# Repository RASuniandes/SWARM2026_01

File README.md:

# SWARM - Sistema de Control para Robot Móvil

## Descripción General

Este repositorio contiene el sistema completo de control para un robot móvil de 4 ruedas omnidireccionales, desarrollado en la Universidad de los Andes. El proyecto integra:

- **Hardware**: ESP32 con 4 motores DC con encoders y drivers L8871
- **Software**: ROS 2 (Robot Operating System) con múltiples modos de control
- **Sensores**: LiDAR YDLidar para navegación autónoma
- **Visión**: MediaPipe para seguimiento de personas

## Estructura del Proyecto

```
SWARM/
├── ros4meetup/              # Paquete principal ROS2
│   ├── ros4meetup/          # Workspace de ROS2
│   │   ├── src/             # Código fuente
│   │   │   ├── ros4meetup/  # Nodos de control
│   │   │   ├── lidar/       # Driver del LiDAR
│   │   │   └── ...          # Otros paquetes
│   │   └── ...              # Build, install, log
│   └── README.md            # Documentación detallada de ROS2
├── CódigoControl/           # Firmware para ESP32 (Arduino)
├── Control SWARM/           # Diseños de PCB (KiCad)
├── Electrónica/             # Esquemáticos y documentación electrónica
├── Dashboard preliminar/    # Interfaz web de monitoreo
└── ojos_frontales/          # Codigo ESP32 para ojos (Matriz 64x2)
```

## Características Principales

### Modos de Control

1. **Vision** (por defecto): Seguimiento de personas usando MediaPipe
2. **Autonomous**: Navegación autónoma con evitación de obstáculos (LiDAR)
3. **Teleop**: Control manual por teclado (W/A/S/D)
4. **Remote**: Control remoto desde ESP32
5. **Web**: Control desde interfaz web

### Arquitectura

```
[Controladores]  →  [Router]  →  [Serial Bridge]  →  [ESP32]  →  [Motores]
                      ↓ cmd_vel
                  [Comandos de velocidad]
```

Cada controlador publica en su propio topic (`vision_command`, `autonomous_command`, etc.). El **Router** selecciona qué controlador está activo y reenvía sus comandos a `cmd_vel`. El **Serial Bridge** convierte estos comandos a JSON y los envía al ESP32 por puerto serial.

## Inicio Rápido

### Requisitos

- Ubuntu 22.04 o superior
- ROS 2 Humble
- Python 3.10+
- Arduino IDE (para firmware ESP32)

### Instalación

1. **Clonar el repositorio:**
```bash
git clone https://github.com/RASuniandes/SWARM.git
cd SWARM/ros4meetup
```

2. **Configurar el entorno ROS2:**
```bash
source ros4meetup/ros.bash
```

3. **Compilar el workspace:**
```bash
cd ros4meetup
colcon build
source install/setup.bash
```

4. **Cargar firmware en ESP32:**
   - Ver documentación en `ros4meetup/firmware/README.md`

### Ejecución

1. **Iniciar el sistema básico:**
```bash
# Terminal 1: Router
ros2 run ros4meetup router

# Terminal 2: Serial Bridge
ros2 run ros4meetup serial_bridge

# Terminal 3: Controlador (elige uno)
ros2 run ros4meetup vision_controller
# o
ros2 run ros4meetup autonomous_controller
# o
ros2 run ros4meetup teleop_controller
```

2. **Cambiar de modo:**
```bash
ros2 topic pub /config std_msgs/String "data: 'autonomous'" --once
```

## Documentación Adicional

- **ROS2 y Nodos**: Ver `ros4meetup/README.md`
- **Firmware ESP32**: Ver `ros4meetup/firmware/README.md`
- **Electrónica**: Ver `Electrónica/`
- **PCB**: Ver `Control SWARM/`

## Desarrollo

### Estructura de Topics ROS2

- `/cmd_vel` (Twist): Comandos de velocidad final al robot
- `/config` (String): Cambio de modo de control
- `/vision_command` (Twist): Comandos del controlador de visión
- `/autonomous_command` (Twist): Comandos del controlador autónomo
- `/teleop_command` (Twist): Comandos del control por teclado
- `/remote_command` (Twist): Comandos remotos desde ESP32
- `/laser_scan` (LaserScan): Datos del LiDAR
- `/esp_feedback` (String): Retroalimentación del ESP32
- `/faces_direction` (String): Dirección para LEDs faciales

### Hardware

- **Microcontrolador**: ESP32
- **Motores**: 4x DC con reductora 1:80 y encoders (12 PPR)
- **Drivers**: L8871 (H-bridge)
- **Sensor**: YDLidar X4
- **Cámara**: USB o CSI para visión

## Licencia

MIT

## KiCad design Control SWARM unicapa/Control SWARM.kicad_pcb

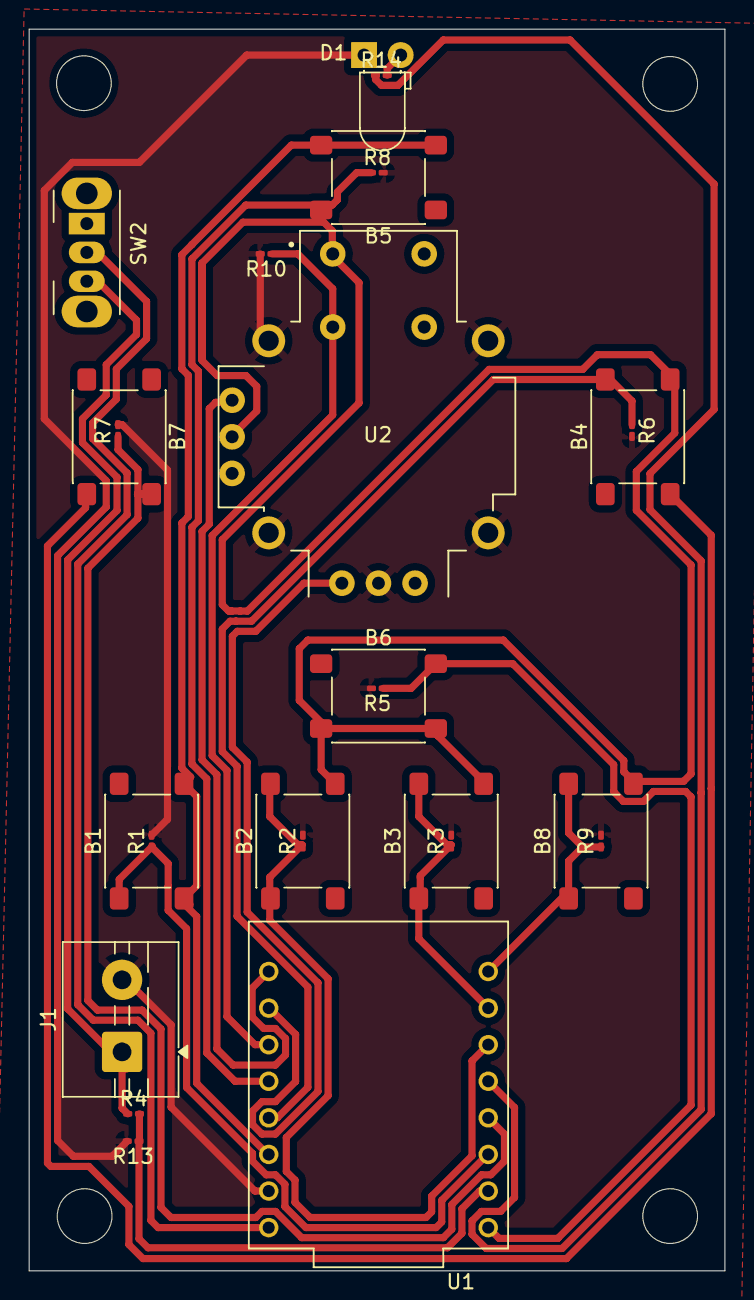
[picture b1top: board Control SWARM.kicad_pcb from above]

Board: 2 copper layers, 48.3 x 86.2 mm, 25 parts (0 on the bottom side), 18 nets.

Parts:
B1: Line Button 1; SW_SPST_PTS645Sx43SMTR92
B2: Line Button 2; SW_SPST_PTS645Sx43SMTR92
B3: Line Button 3; SW_SPST_PTS645Sx43SMTR92
B4: Radial Button 2; SW_SPST_PTS645Sx43SMTR92
B5: Radial Button 1; SW_SPST_PTS645Sx43SMTR92
B6: Radial Button 3; SW_SPST_PTS645Sx43SMTR92
B7: Radial Button 4; SW_SPST_PTS645Sx43SMTR92
B8: Line Button 4; SW_SPST_PTS645Sx43SMTR92
D1: LED; LED_D3.0mm_Horizontal_O1.27mm_Z2.0mm_Clear
J1: Screw_Terminal_01x02; TerminalBlock_MaiXu_MX126-5.0-02P_1x02_P5.00mm
R1: RL1; R_0201_0603Metric_Pad0.64x0.40mm_HandSolder
R2: RL2; R_0201_0603Metric_Pad0.64x0.40mm_HandSolder
R3: RL3; R_0201_0603Metric_Pad0.64x0.40mm_HandSolder
R4: RVD1; R_0201_0603Metric_Pad0.64x0.40mm_HandSolder
R5: RR3; R_0201_0603Metric_Pad0.64x0.40mm_HandSolder
R6: RR2; R_0201_0603Metric_Pad0.64x0.40mm_HandSolder
R7: RR4; R_0201_0603Metric_Pad0.64x0.40mm_HandSolder
R8, R10: RR1; R_0201_0603Metric_Pad0.64x0.40mm_HandSolder
R9: RL4; R_0201_0603Metric_Pad0.64x0.40mm_HandSolder
R13: RVD2; R_0201_0603Metric_Pad0.64x0.40mm_HandSolder
R14: LEDR; R_0201_0603Metric_Pad0.64x0.40mm_HandSolder
SW2: SW_SPDT; SW_Slide_SPDT_Angled_CK_OS102011MA1Q
U1: ESP32-C3_MINI; MODULE_ESP32-C3_SUPERMINI_TH
U2: JOYSTICK; XDCR_COM-09032

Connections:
+3.3V: B1.2, B2.2, B3.2, B4.2, B5.2, B6.2, B7.2, B8.2, U1.3.3 (3V3), U2.B1A (SEL+), U2.V2 (V)
+3.6V: J1.1, R4.1, SW2.3 (C)
/GPIO0 A0: U1.0 (GPIO0), U2.V1 (V+)
/GPIO1 A1: U1.1 (GPIO1), U2.H1 (H+)
/GPIO2 A2: R10.1, U1.2 (GPIO2), U2.B2A (SEL-)
/GPIO3 A3: B5.1, R8.1, U1.3 (GPIO3)
/GPIO4 A4 SCK: B4.1, R6.1, U1.4 (GPIO4)
/GPIO5 A5 MISO: B6.1, R5.1, U1.5 (GPIO5)
/GPIO6 MOSI: R4.2, R13.1, U1.6 (GPIO6)
/GPIO7 SS: B1.1, R1.1, U1.7 (GPIO7)
/GPIO8 SDA: B7.1, R7.1, U1.8 (GPIO8)
/GPIO9 SCL: R14.1, U1.9 (GPIO9)
/GPIO10: B2.1, R2.1, U1.10 (GPIO10)
/GPIO20 RX: B3.1, R3.1, U1.20 (GPIO20)
/GPIO21 TX: B8.1, R9.1, U1.21 (GPIO21)
/VOLTAGE REGULATED: SW2.2 (B), U1.5V
GND: D1.1 (K), J1.2, R1.2, R2.2, R3.2, R5.2, R6.2, R7.2, R8.2, R9.2, R10.2, R13.2, U1.G (GND), U2.H2 (H), U2.S1 (SHIELD), U2.S2 (SHIELD), U2.S3 (SHIELD), U2.S4 (SHIELD)
unnamed: D1.2 (A), R14.2

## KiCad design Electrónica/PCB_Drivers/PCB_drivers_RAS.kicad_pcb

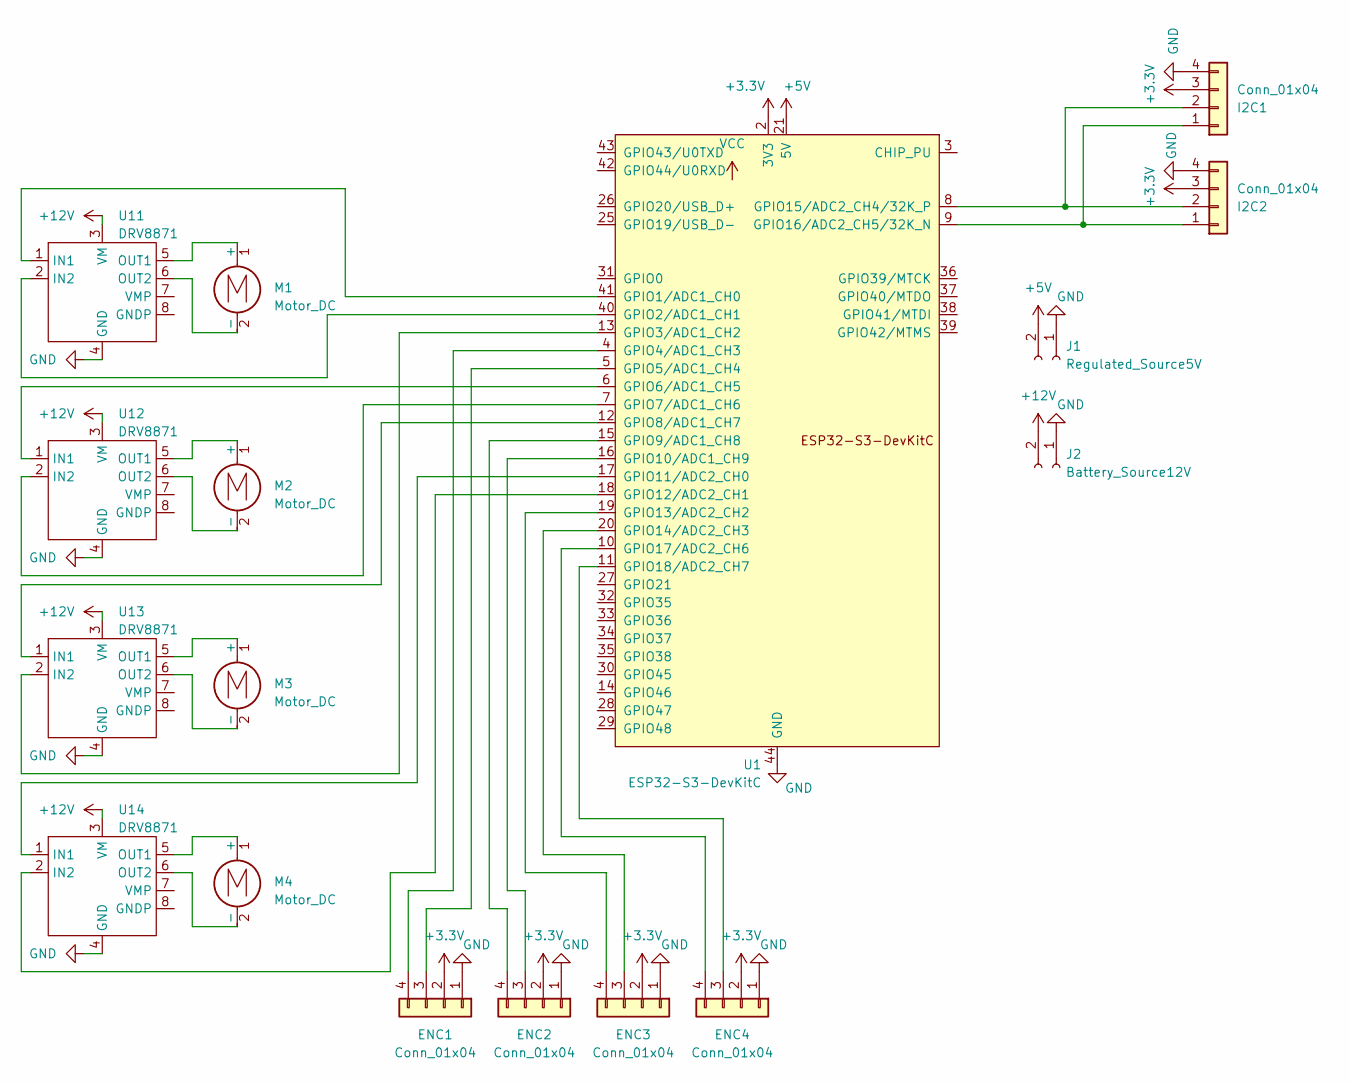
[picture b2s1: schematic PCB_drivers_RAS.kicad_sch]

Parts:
ENC1, ENC2, ENC3, ENC4: Conn_01x04; PinSocket_1x04_P2.54mm_Vertical
I2C1, I2C2: Conn_01x04; PinSocket_1x04_P2.54mm_Vertical
J1: Regulated_Source5V; PinSocket_1x02_P2.00mm_Vertical
J2: Battery_Source12V; PinSocket_1x02_P2.54mm_Vertical
M1, M2, M3, M4: Motor_DC; PinHeader_2x01_P2.54mm_Vertical
U1: ESP32-S3-DevKitC
U11, U12, U13, U14: DRV8871; DRV8871-MODULE

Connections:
+3.3V: ENC1.2, ENC2.2, ENC3.2, ENC4.2, I2C1.3, I2C2.3, U1.1 (3V3), U1.2 (3V3)
+5V: J1.2, U1.21 (5V)
+12V: J2.2, U11.3 (VM), U12.3 (VM), U13.3 (VM), U14.3 (VM)
GND: ENC1.1, ENC2.1, ENC3.1, ENC4.1, I2C1.4, I2C2.4, J1.1, J2.1, U1.22 (GND), U1.23 (GND), U1.24 (GND), U1.44 (GND), U11.4 (GND), U12.4 (GND), U13.4 (GND), U14.4 (GND)
unnamed: ENC1.3, U1.5 (GPIO5/ADC1_CH4)
unnamed: ENC1.4, U1.4 (GPIO4/ADC1_CH3)
unnamed: ENC2.3, U1.16 (GPIO10/ADC1_CH9)
unnamed: ENC2.4, U1.15 (GPIO9/ADC1_CH8)
unnamed: ENC3.3, U1.20 (GPIO14/ADC2_CH3)
unnamed: ENC3.4, U1.19 (GPIO13/ADC2_CH2)
unnamed: ENC4.3, U1.11 (GPIO18/ADC2_CH7)
unnamed: ENC4.4, U1.10 (GPIO17/ADC2_CH6)
unnamed: I2C1.1, I2C2.1, U1.9 (GPIO16/ADC2_CH5/32K_N)
unnamed: I2C1.2, I2C2.2, U1.8 (GPIO15/ADC2_CH4/32K_P)
unnamed: M1.1 (+), U11.5 (OUT1)
unnamed: M1.2 (-), U11.6 (OUT2)
unnamed: M2.1 (+), U12.5 (OUT1)
unnamed: M2.2 (-), U12.6 (OUT2)
unnamed: M3.1 (+), U13.5 (OUT1)
unnamed: M3.2 (-), U13.6 (OUT2)
unnamed: M4.1 (+), U14.5 (OUT1)
unnamed: M4.2 (-), U14.6 (OUT2)
unnamed: U1.41 (GPIO1/ADC1_CH0), U11.1 (IN1)
unnamed: U1.40 (GPIO2/ADC1_CH1), U11.2 (IN2)
unnamed: U1.13 (GPIO3/ADC1_CH2), U13.2 (IN2)
unnamed: U1.6 (GPIO6/ADC1_CH5), U12.1 (IN1)
unnamed: U1.7 (GPIO7/ADC1_CH6), U12.2 (IN2)
unnamed: U1.12 (GPIO8/ADC1_CH7), U13.1 (IN1)
unnamed: U1.17 (GPIO11/ADC2_CH0), U14.1 (IN1)
unnamed: U1.18 (GPIO12/ADC2_CH1), U14.2 (IN2)

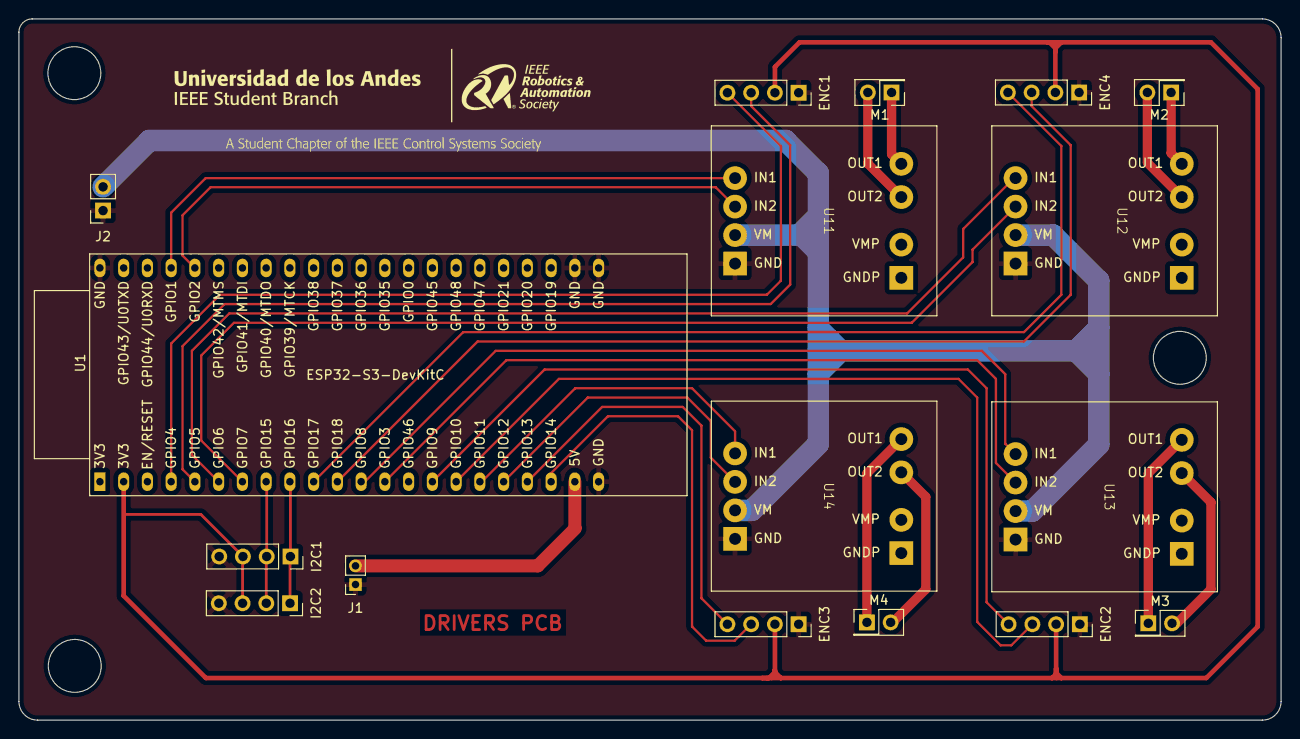
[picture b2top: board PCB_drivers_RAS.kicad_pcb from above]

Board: 2 copper layers, 135.0 x 75.0 mm, 17 parts (0 on the bottom side), 30 nets.

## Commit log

2026-03-16 Import
2026-04-27 microros
2026-06-29 Re-initializing repo after VM crash
